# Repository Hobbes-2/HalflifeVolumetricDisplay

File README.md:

Halflife Linear Volumetric Display

This project is for week 4 of Hackclub Half-life; displays. It is a 8x8 matrix attached to a motor that moves it up and down, running off of an Orpheus Pico. I orginally wanted to make this a spinning display, but then I would have had to use slip rings, which I didnt have time to implement (when do i ever).
Im taking some inspiration from this video (https://www.youtube.com/watch?v=KgT20tHpk1g), but adjusting the model a bit. This is a project Id actually really like to iterate and improve upon once i build it once. The hardest part of this project was honestly the CAD, as the dimensions and mechanical works of it had to be somewhat precise.

Without further adeu, my (definently well made) parts.

Schematic

PCB

3D

CAD

## Bill of Materials

| # | Part / Component | Quantity | Price (USD) | Purchase Link |
|---:|---|---:|---:|---|
| 1 | 8x8 Display | 1 | $12.22 | [DigiKey](https://www.digikey.com/en/products/detail/boardoza/B0501V10000175/30278350) |
| 2 | RF5000 Motor | 1 | $11.55 | [DigiKey](https://www.digikey.com/en/products/detail/mabuchi-motor/RF500TB-12560/29784571) |
| 3 | IRLZ44NPBF Transistor | 1 | $1.80 | [DigiKey](https://www.digikey.com/en/products/detail/infineon-technologies/IRLZ44NPBF/811808) |
| 4 | 1N4007 Diode | 1 | $0.14 | [DigiKey](https://www.digikey.com/en/products/detail/diotec-semiconductor/1N4007/18833652) |
| 5 | 220kΩ Resistor | 1 | $0.10 | [DigiKey](https://www.digikey.com/en/products/detail/stackpole-electronics-inc/CF18JT220K/1741641) |
| 6 | 10kΩ Resistor | 1 | $0.10 | [DigiKey](https://www.digikey.com/en/products/detail/stackpole-electronics-inc/CF18JT10K0/1741566) |
| 7 | 330Ω Resistor | 1 | $0.10 | [DigiKey](https://www.digikey.com/en/products/detail/stackpole-electronics-inc/CF14JT330R/1741399) |
| 8 | 74AHCT125 Logic IC | 1 | $0.95 | [DigiKey](https://www.digikey.com/en/products/detail/texas-instruments/SN74AHCT125N/375798) |
| 9 | 100nF Capacitor | 1 | $0.11 | [DigiKey](https://www.digikey.com/en/products/detail/murata-electronics/GRM033R60J104KE19D/702433) |
| 10 | Raspberry Pi Pico | 1 | $5.00 | [Adafruit](https://www.adafruit.com/product/5525) |
| 11 | Terminal Connectors | 2 | $1.06 | [DigiKey](https://www.digikey.com/en/products/detail/same-sky-formerly-cui-devices/TB007-508-02BE/10064127) |
| 12 | PCB | 1 | $11.43 | [JLCPCB](https://cart.jlcpcb.com/shopcart/cart/) |
| 13 | CAD / 3D Printing | 1 | $6.00 | [PrintLegion](https://printlegion.hackclub.com/printers) |
| 14 | Screws | 100 | $4.92 | [DigiKey](https://www.digikey.com/en/products/detail/bfirst-industrial/MPMS-003-0005-PH/274953) |

### Cost Summary

**Total Project Cost: $55.48 USD (tax included).**

! Formatted with AI
Not all parts were bought for this project - some I already had

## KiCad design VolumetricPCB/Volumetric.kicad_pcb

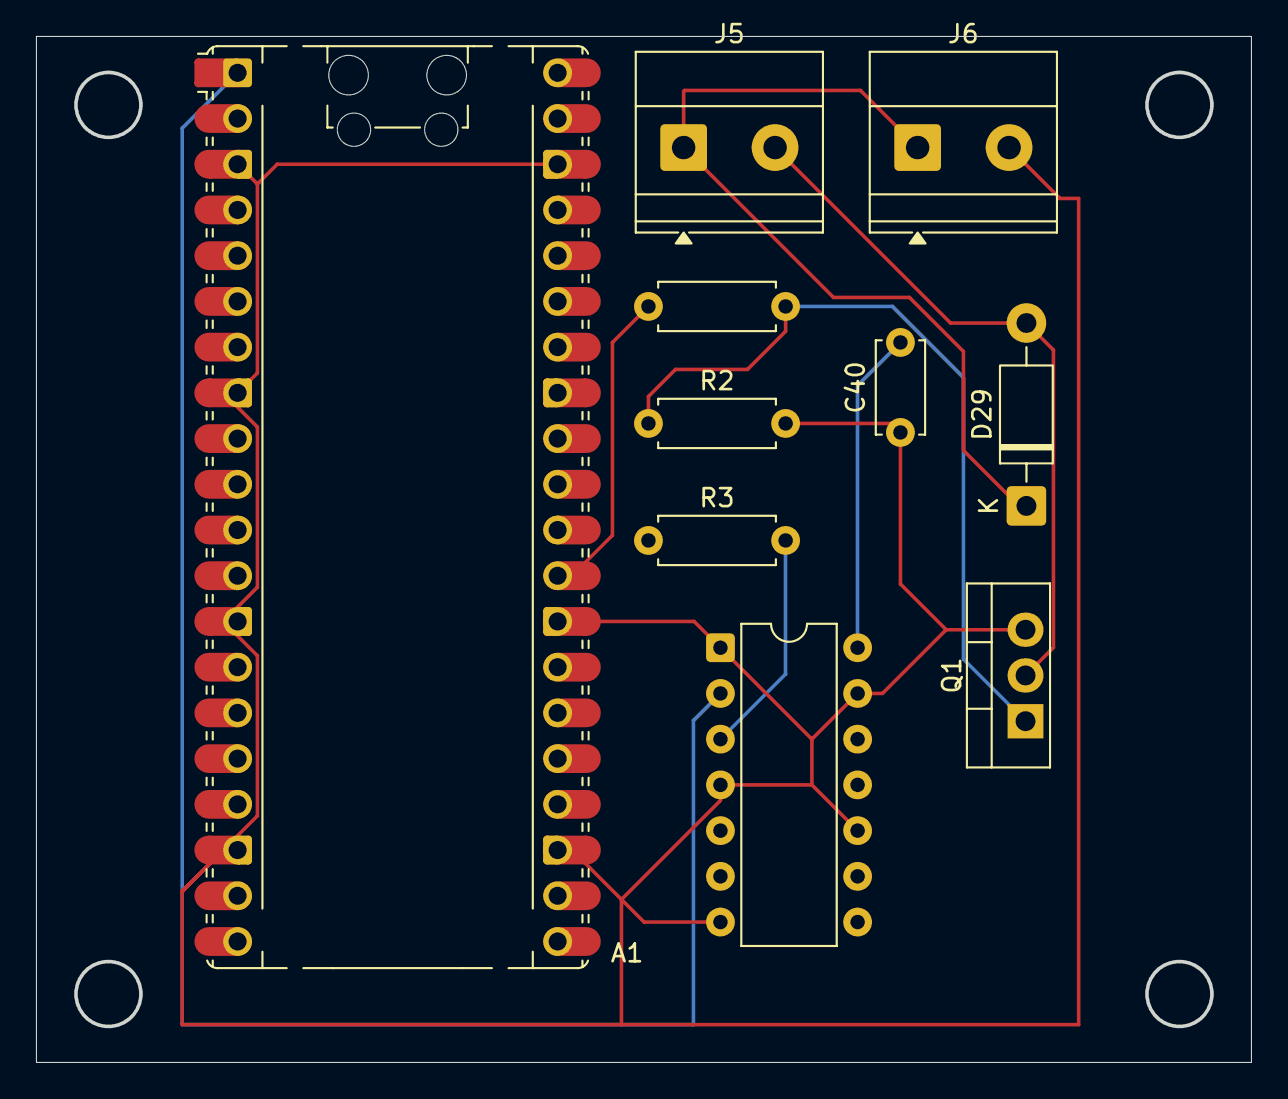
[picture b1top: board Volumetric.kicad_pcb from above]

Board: 2 copper layers, 67.5 x 57.0 mm, 10 parts (0 on the bottom side), 8 nets.

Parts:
A1: RaspberryPi_Pico; RaspberryPi_Pico_Common_Unspecified
C40: 100nf; C_Disc_D5.0mm_W2.5mm_P5.00mm
D29: 1N4007; D_DO-41_SOD81_P10.16mm_Horizontal
J5: Motor; TerminalBlock_Phoenix_MKDS-1,5-2-5.08_1x02_P5.08mm_Horizont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
J6: Battery; TerminalBlock_Phoenix_MKDS-1,5-2-5.08_1x02_P5.08mm_Horizont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
Q1: IRLZ44N; TO-220-3_Vertical
R1: 220k; R_Axial_DIN0207_L6.3mm_D2.5mm_P7.62mm_Horizontal
R2: 10k; R_Axial_DIN0207_L6.3mm_D2.5mm_P7.62mm_Horizontal
R3: 330; R_Axial_DIN0207_L6.3mm_D2.5mm_P7.62mm_Horizontal
U1: 74AHCT125; DIP-14_W7.62mm

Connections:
22: A1.29 (GPIO22), R1.1
+5V: C40.2, U1.14 (VCC)
GND: A1.3 (GND), A1.8 (GND), A1.13 (GND), A1.18 (GND), A1.23 (GND), A1.28 (GND), A1.38 (GND), C40.1, J6.2, Q1.3 (S), R2.2, U1.1, U1.4, U1.7 (GND), U1.10, U1.13
unnamed: A1.1 (GPIO0), U1.2
unnamed: D29.2 (A), J5.2, Q1.2 (D)
unnamed: D29.1 (K), J5.1, J6.1
unnamed: Q1.1 (G), R1.2, R2.1
unnamed: R3.2, U1.3

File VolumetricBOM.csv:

Part,Number,Price,Link
8x8 Display,1,12.22,https://www.digikey.com/en/products/detail/boardoza/B0501V10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
RF5000 Motor,1,11.55,https://www.digikey.com/en/products/detail/mabuchi-motor/RF5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
IRLZ44NPBF Transistor,1,1.8,https://www.digikey.com/en/products/detail/infineon-technolo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
1N4007 Diode,1,0.14,https://www.digikey.com/en/products/detail/diotec-semiconduc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
Resistor 220k,1,0.1,https://www.digikey.com/en/products/detail/stackpole-electro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
Resistor 10k,1,0.1,https://www.digikey.com/en/products/detail/stackpole-electro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
Resistor 330,1,0.1,https://www.digikey.com/en/products/detail/stackpole-electro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
74AHCT125,1,0.95,https://www.digikey.com/en/products/detail/texas-instruments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
Capacitor 100nf,1,0.11,https://www.digikey.com/en/products/detail/murata-electronic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
Raspberry Pi Pico,1,5,https://www.adafruit.com/product/5525?src=raspberrypi
Terminal connectors,2,1.06,https://www.digikey.com/en/products/detail/same-sky-formerly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
PCB,1,11.43,https://cart.jlcpcb.com/shopcart/cart/
CAD,1,6,https://printlegion.hackclub.com/printers
Screws,100,4.92,https://www.digikey.com/en/products/detail/bfirst-industrial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
,,,
Total,,55.48,(Tax accounted)
